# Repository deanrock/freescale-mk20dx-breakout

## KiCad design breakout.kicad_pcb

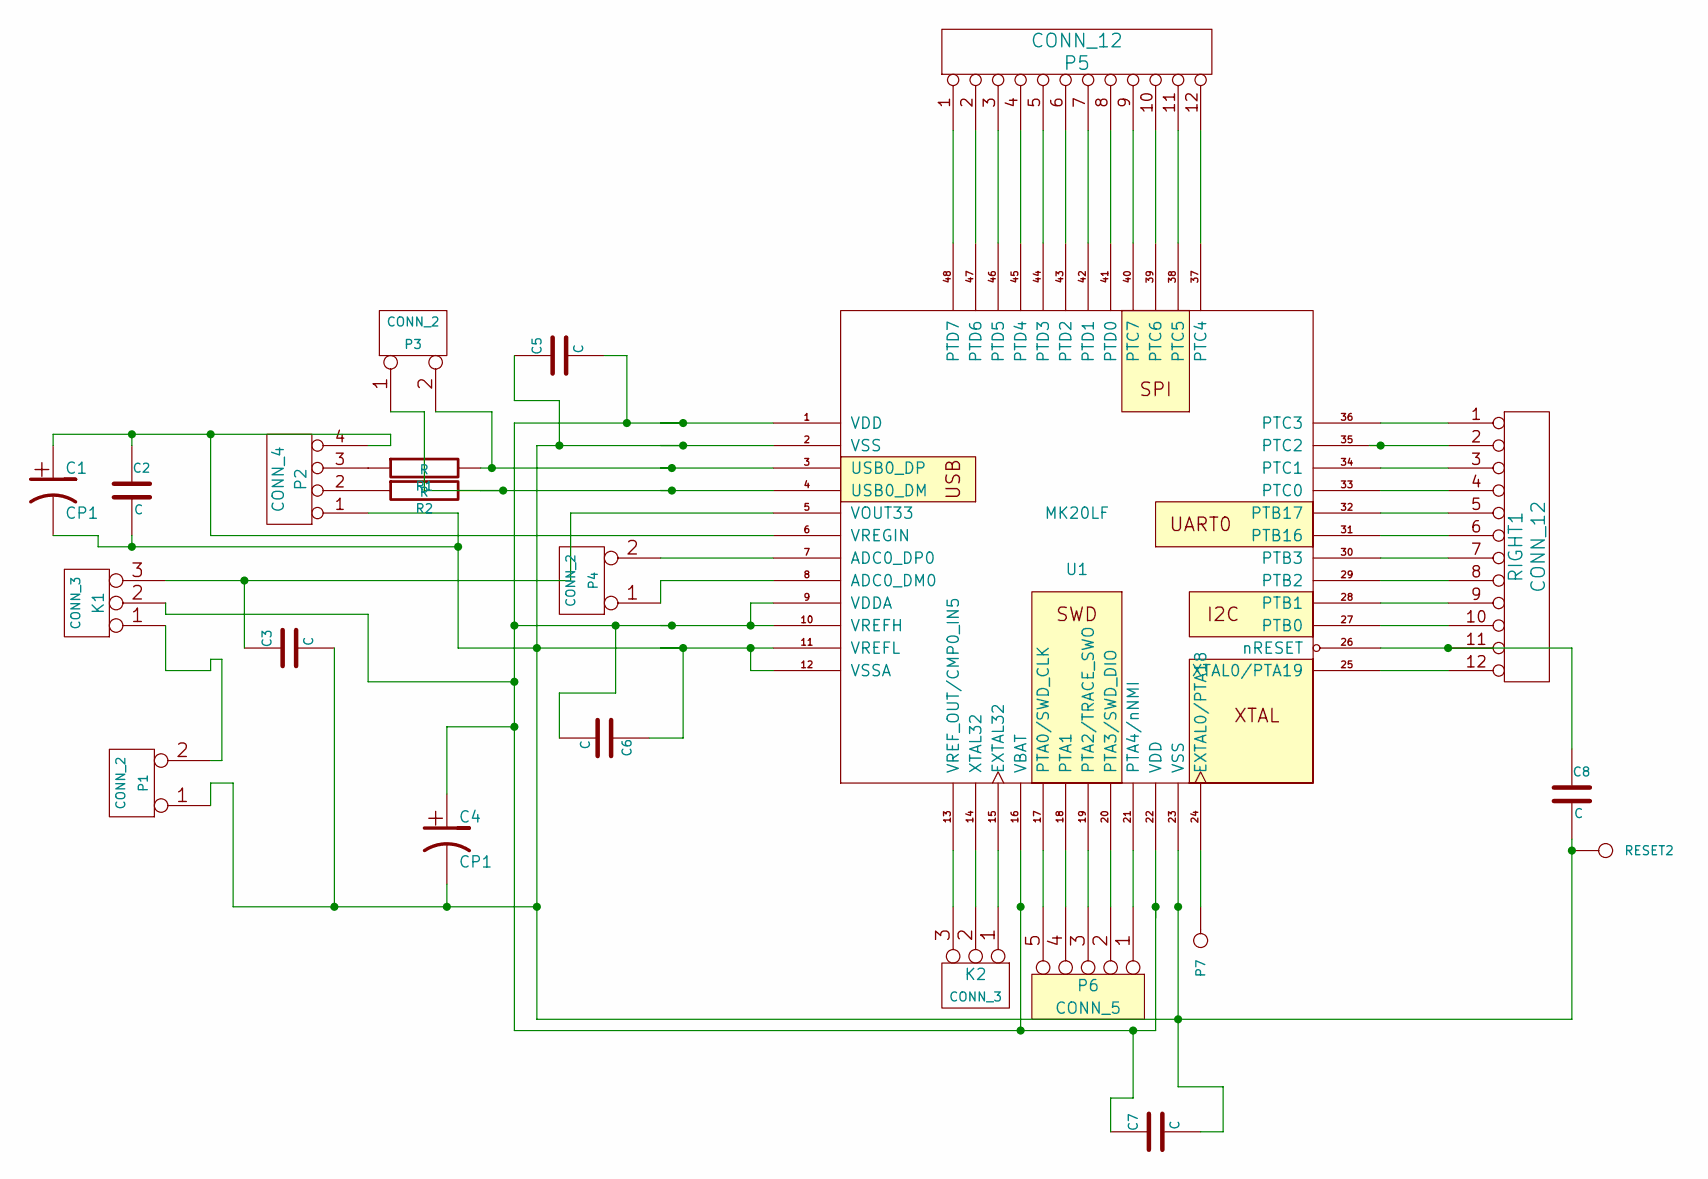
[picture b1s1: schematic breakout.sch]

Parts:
C1, C4: CP1
C2, C3, C5, C6, C7, C8: C
K1, K2: CONN_3
P1, P3, P4: CONN_2
P2: CONN_4
P5: CONN_12
P6: CONN_5
P7: CONN_1
R1, R2: R
RESET2: CONN_1
RIGHT1: CONN_12
U1: MK20LF

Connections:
unnamed: RIGHT1.7, U1.30 (PTB3)
unnamed: RIGHT1.5, U1.32 (PTB17)
unnamed: RIGHT1.6, U1.31 (PTB16)
unnamed: K1.1, P1.2 (PM)
unnamed: P5.7, U1.42 (PTD1)
unnamed: P5.8, U1.41 (PTD0)
unnamed: P5.9, U1.40 (PTC7)
unnamed: P4.1, U1.8 (ADC0_DM0)
unnamed: C4.1, C5.2, C6.2, C7.1, K1.2 (PM), U1.1 (VDD), U1.9 (VDDA), U1.10 (VREFH), U1.16 (VBAT), U1.22 (VDD)
unnamed: C3.1, K1.3, U1.5 (VOUT33)
unnamed: P4.2 (PM), U1.7 (ADC0_DP0)
unnamed: P2.3, R1.1
unnamed: P2.2, R2.1
unnamed: C1.2, C2.2, C3.2, C4.2, C5.1, C6.1, C7.2, C8.2, P1.1, P2.1, RESET2.1, U1.2 (VSS), U1.11 (VREFL), U1.12 (VSSA), U1.23 (VSS)
unnamed: P6.1, U1.21 (PTA4/nNMI)
unnamed: P6.2, U1.20 (PTA3/SWD_DIO)
unnamed: P5.5, U1.44 (PTD3)
unnamed: P5.3, U1.46 (PTD5)
unnamed: RIGHT1.1, U1.36 (PTC3)
unnamed: P5.4, U1.45 (PTD4)
unnamed: RIGHT1.2, U1.35 (PTC2)
unnamed: RIGHT1.12, U1.25 (XTAL0/PTA19)
unnamed: P6.5, U1.17 (PTA0/SWD_CLK)
unnamed: RIGHT1.3, U1.34 (PTC1)
unnamed: P5.6, U1.43 (PTD2)
unnamed: RIGHT1.4, U1.33 (PTC0)
unnamed: RIGHT1.10, U1.27 (PTB0)
unnamed: P5.12, U1.37 (PTC4)
unnamed: P5.2, U1.47 (PTD6)
unnamed: P6.4, U1.18 (PTA1)
unnamed: RIGHT1.9, U1.28 (PTB1)
unnamed: P5.11, U1.38 (PTC5)
unnamed: P5.1, U1.48 (PTD7)
unnamed: P6.3, U1.19 (PTA2/TRACE_SWO)
unnamed: RIGHT1.8, U1.29 (PTB2)
unnamed: P5.10, U1.39 (PTC6)
unnamed: K2.1, U1.15 (EXTAL32)
unnamed: K2.2 (PM), U1.14 (XTAL32)
unnamed: K2.3, U1.13 (VREF_OUT/CMP0_IN5)
unnamed: P7.1, U1.24 (EXTAL0/PTA18)
unnamed: P3.2 (PM), R1.2, U1.3 (USB0_DP)
unnamed: P3.1, R2.2, U1.4 (USB0_DM)
unnamed: C1.1, C2.1, P2.4, U1.6 (VREGIN)

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
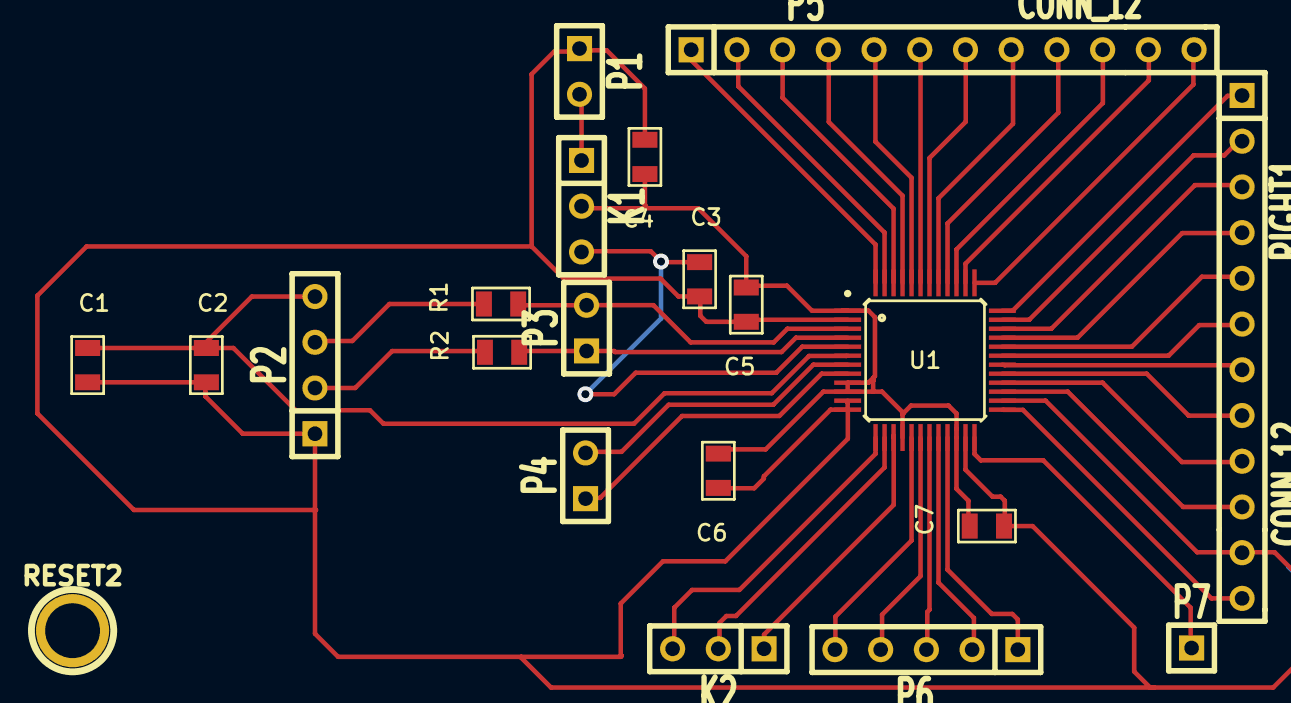
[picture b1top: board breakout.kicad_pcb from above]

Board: 2 copper layers, 22 parts (1 on the bottom side), 44 nets.

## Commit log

2013-08-22 almost finished v1
2013-08-23 finished board
